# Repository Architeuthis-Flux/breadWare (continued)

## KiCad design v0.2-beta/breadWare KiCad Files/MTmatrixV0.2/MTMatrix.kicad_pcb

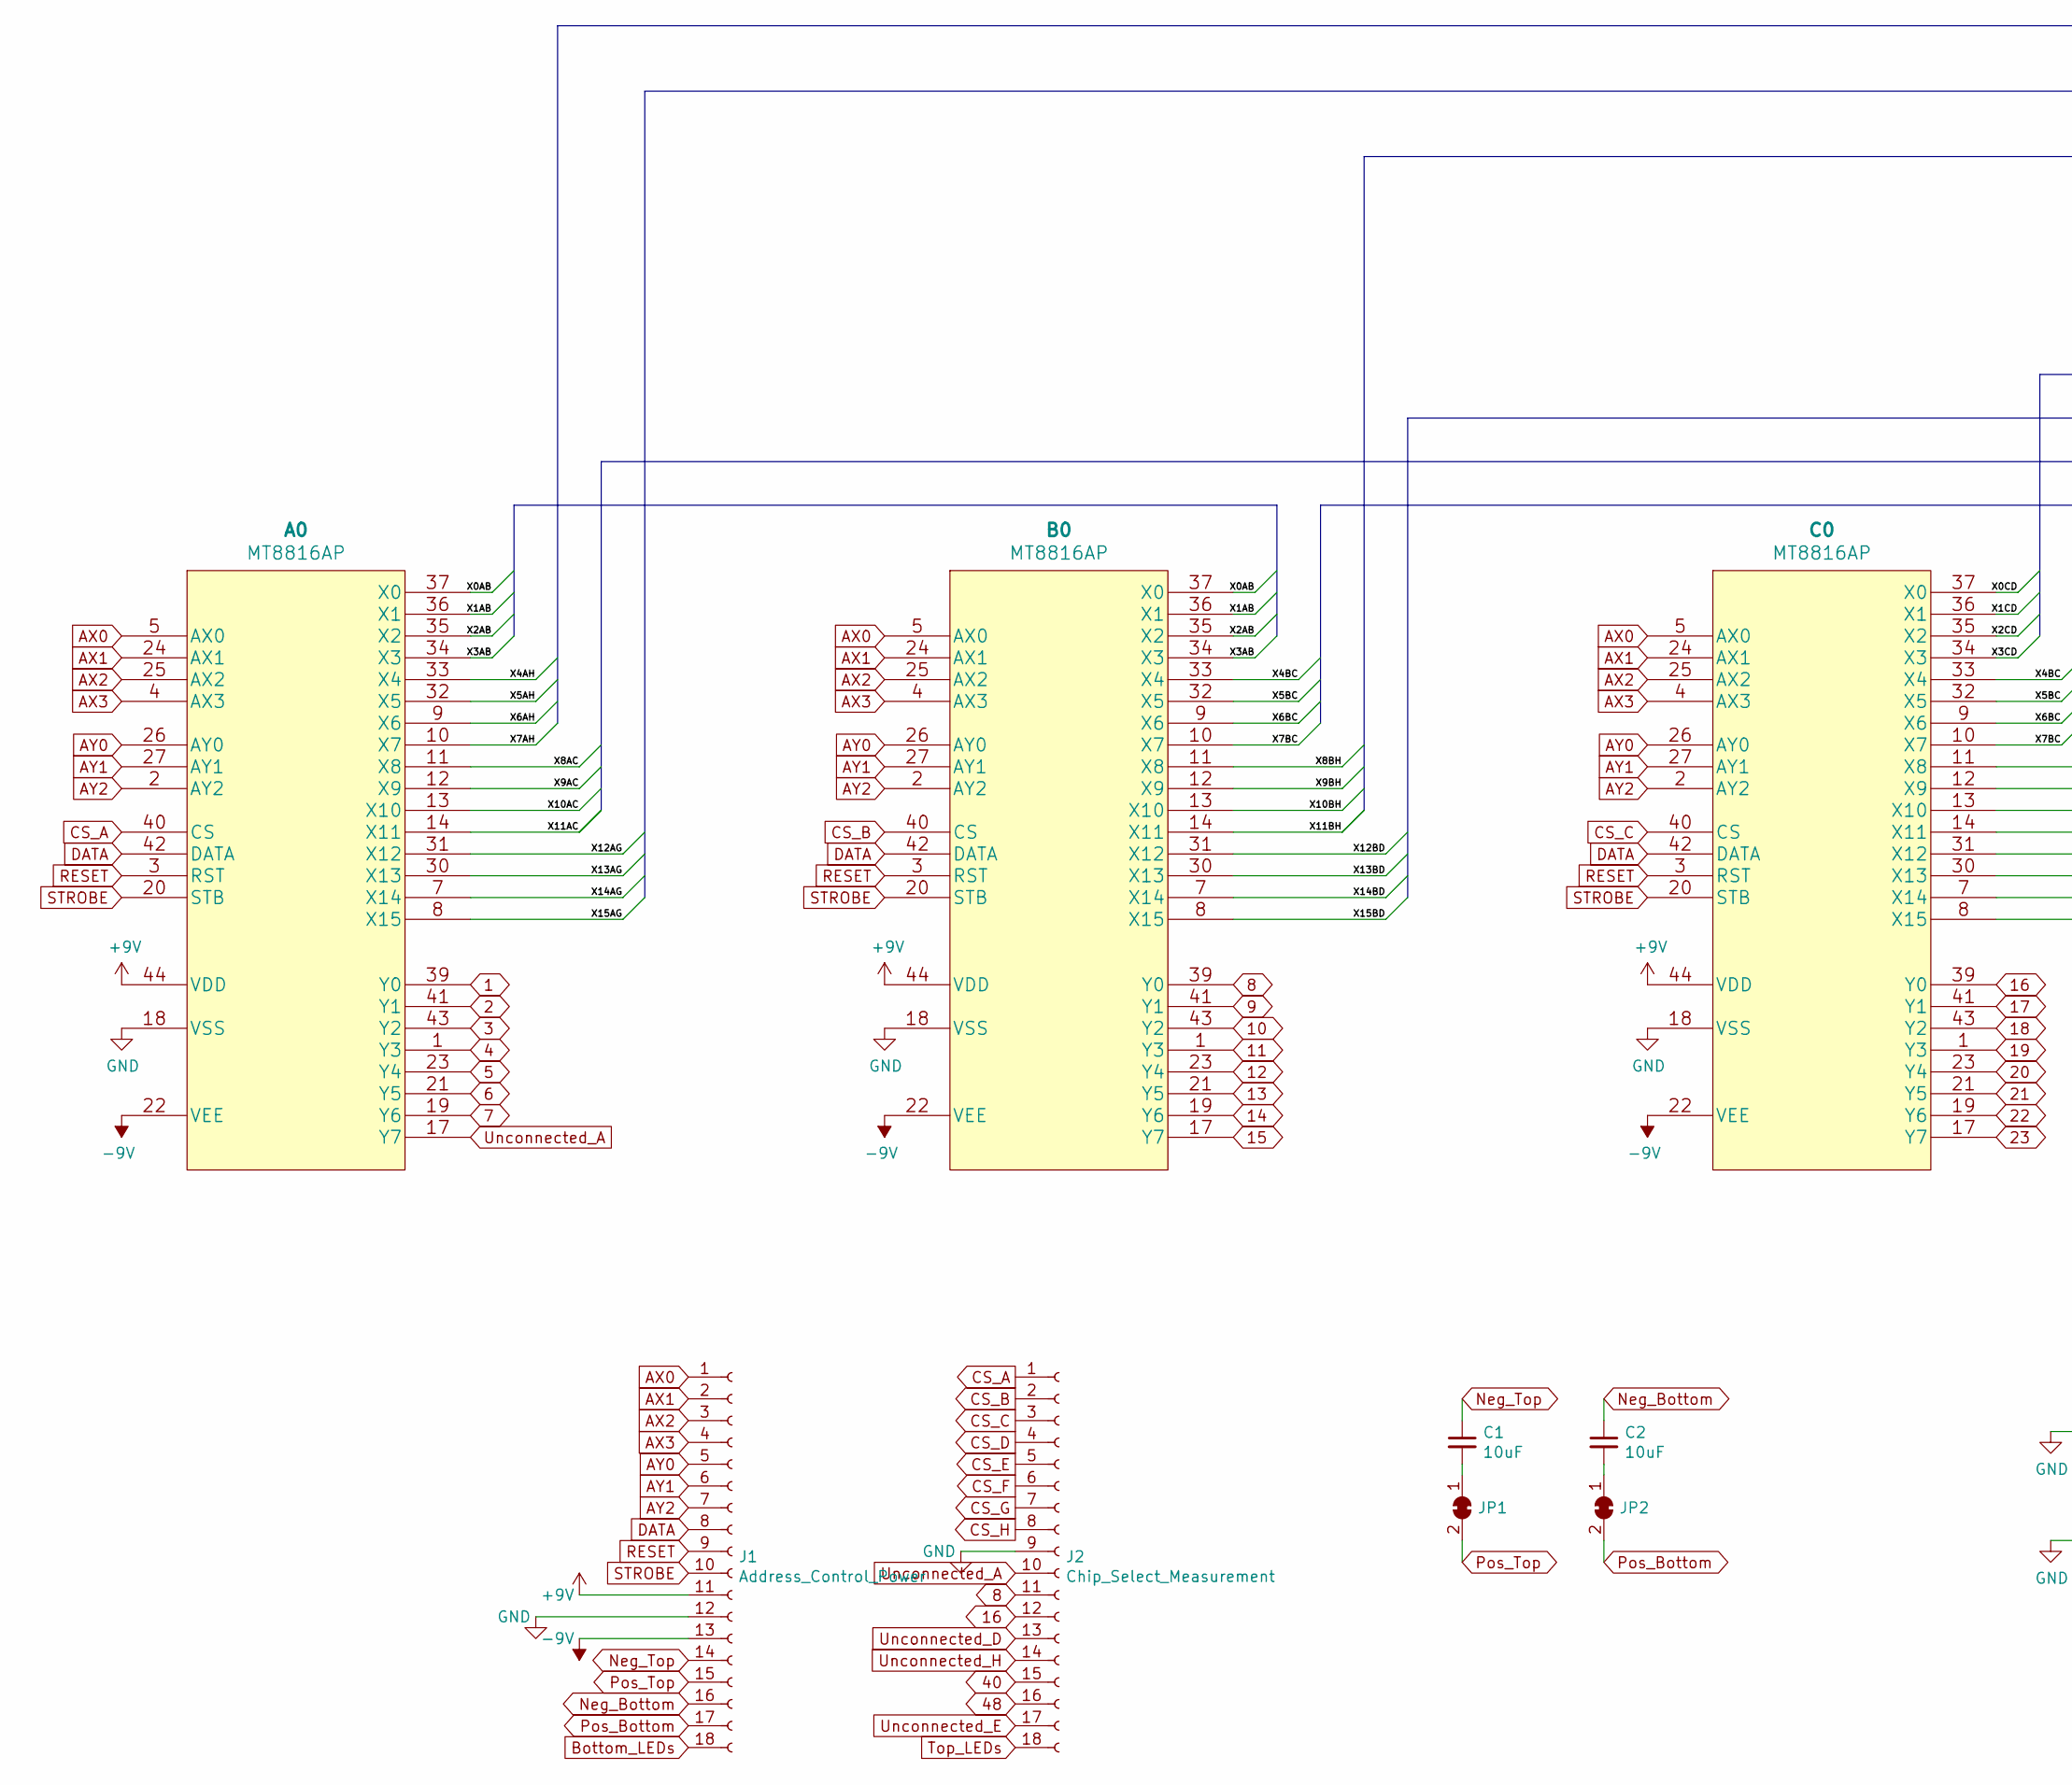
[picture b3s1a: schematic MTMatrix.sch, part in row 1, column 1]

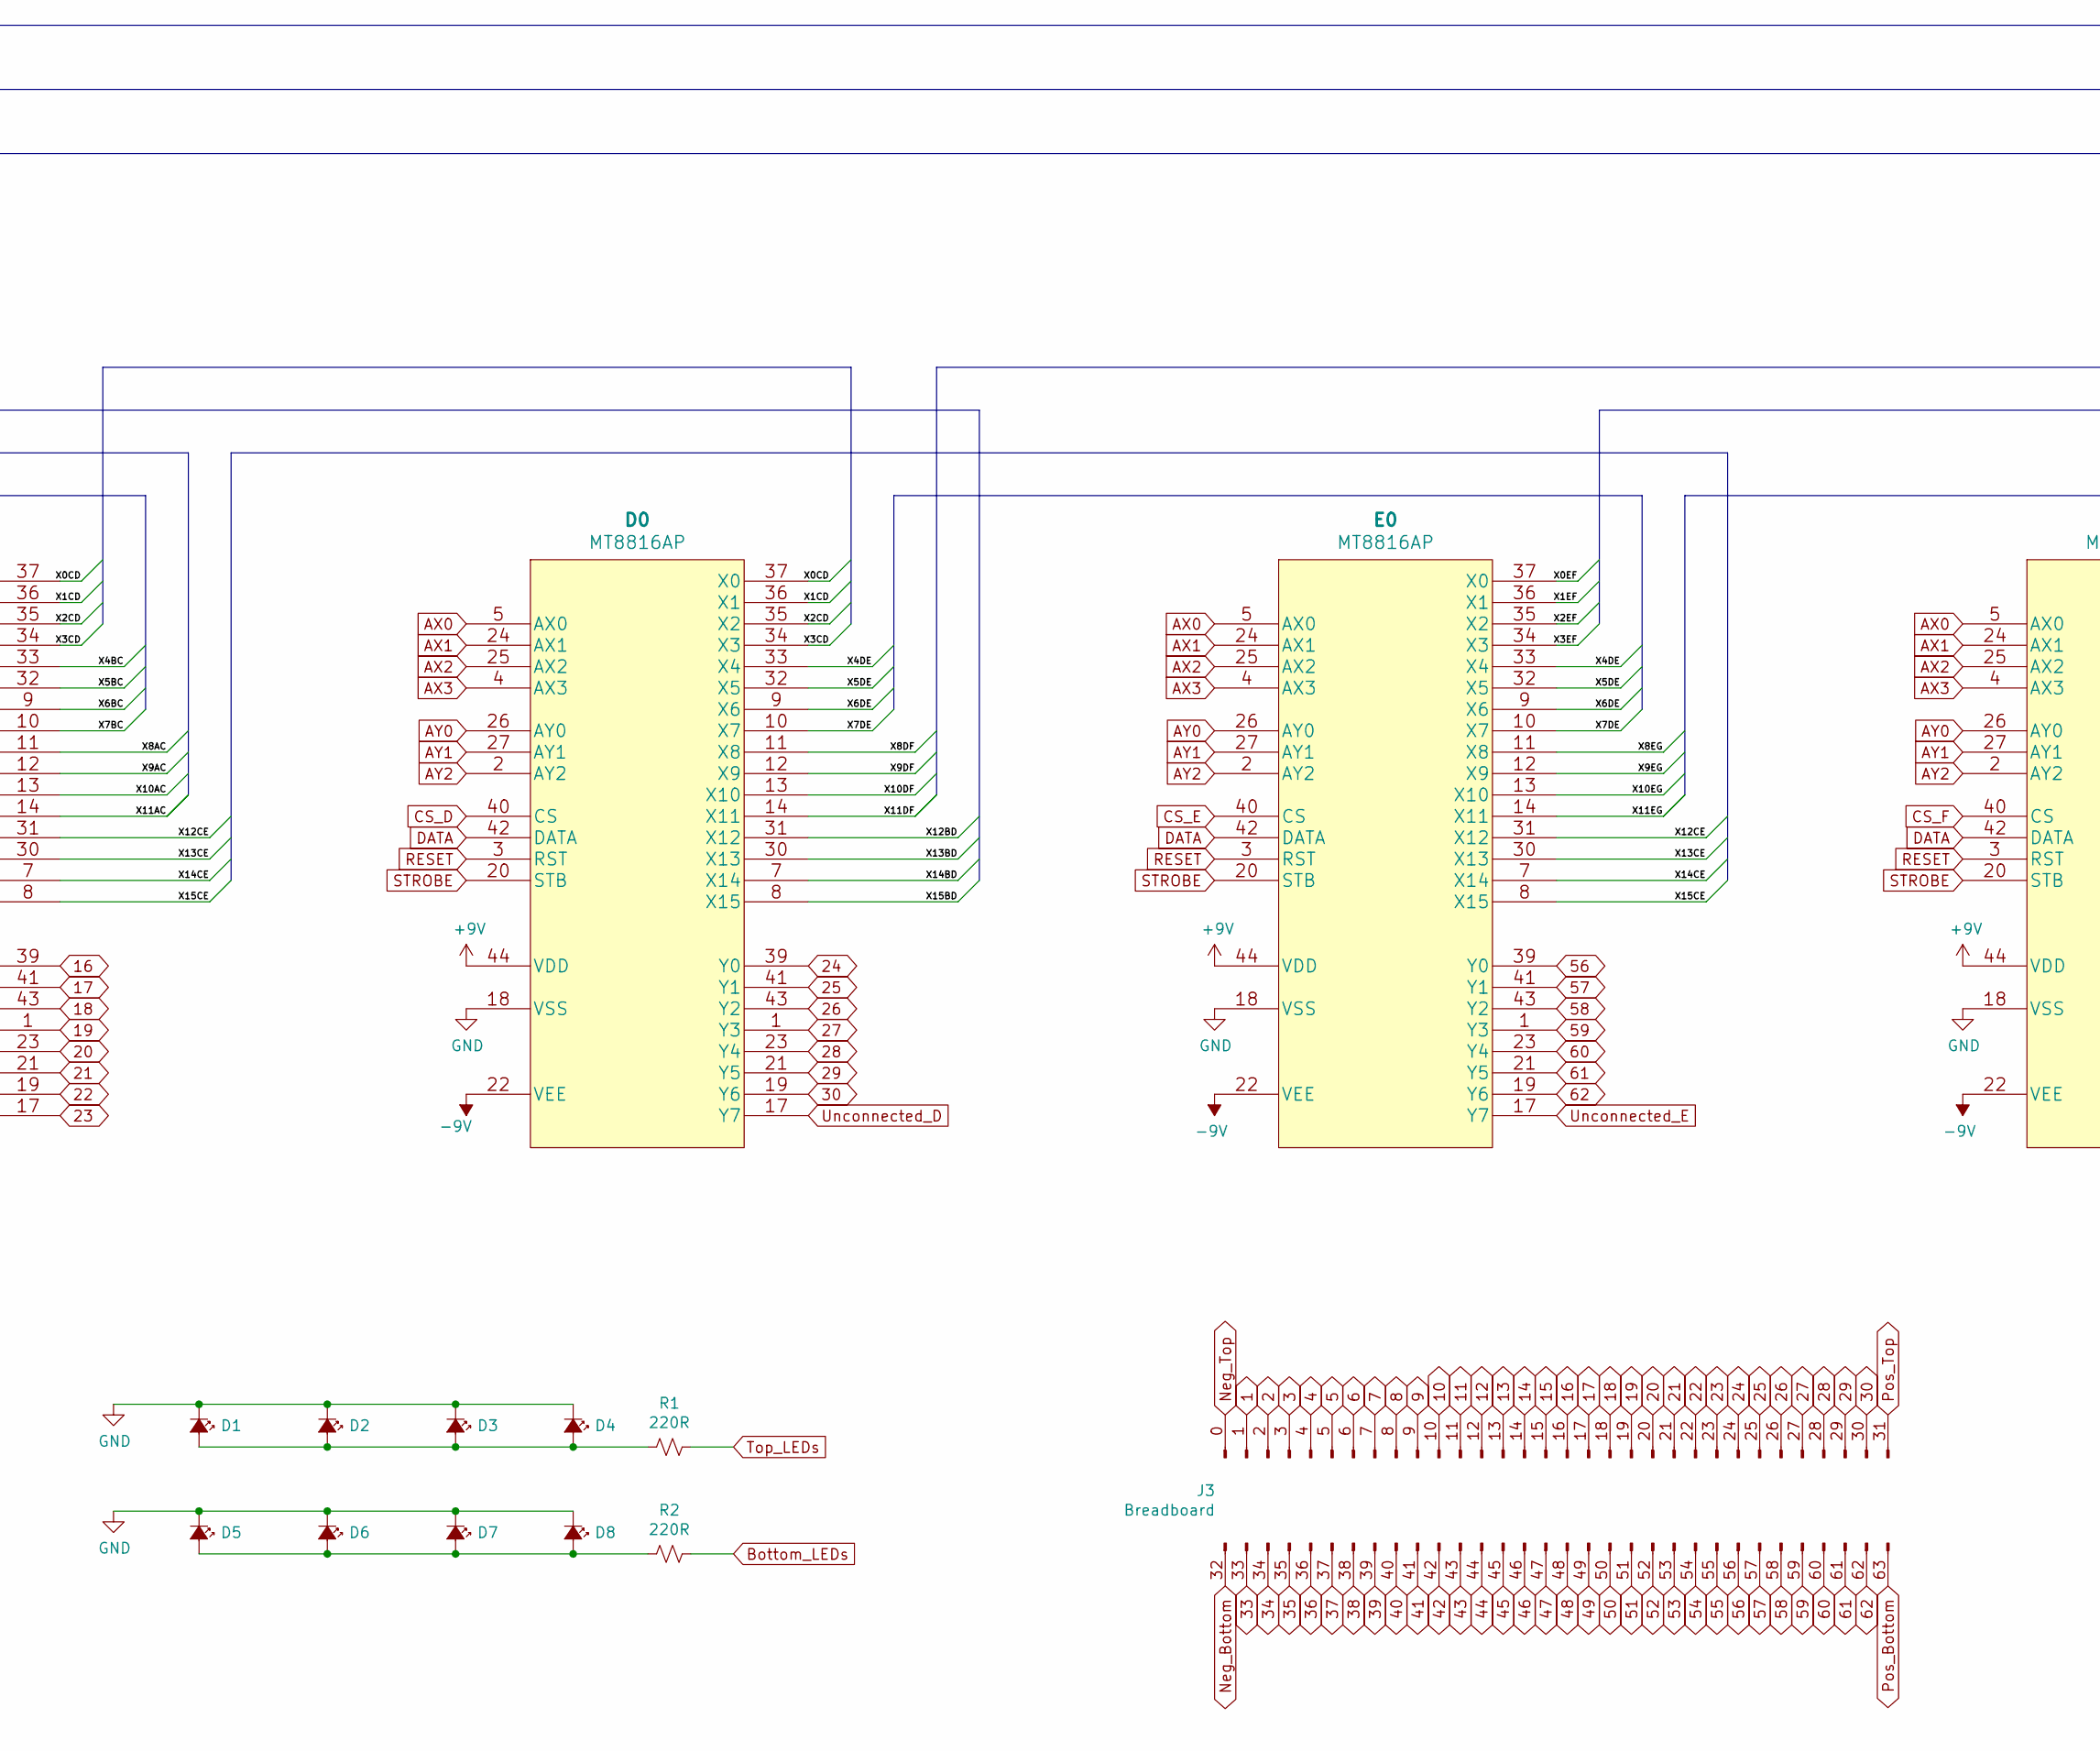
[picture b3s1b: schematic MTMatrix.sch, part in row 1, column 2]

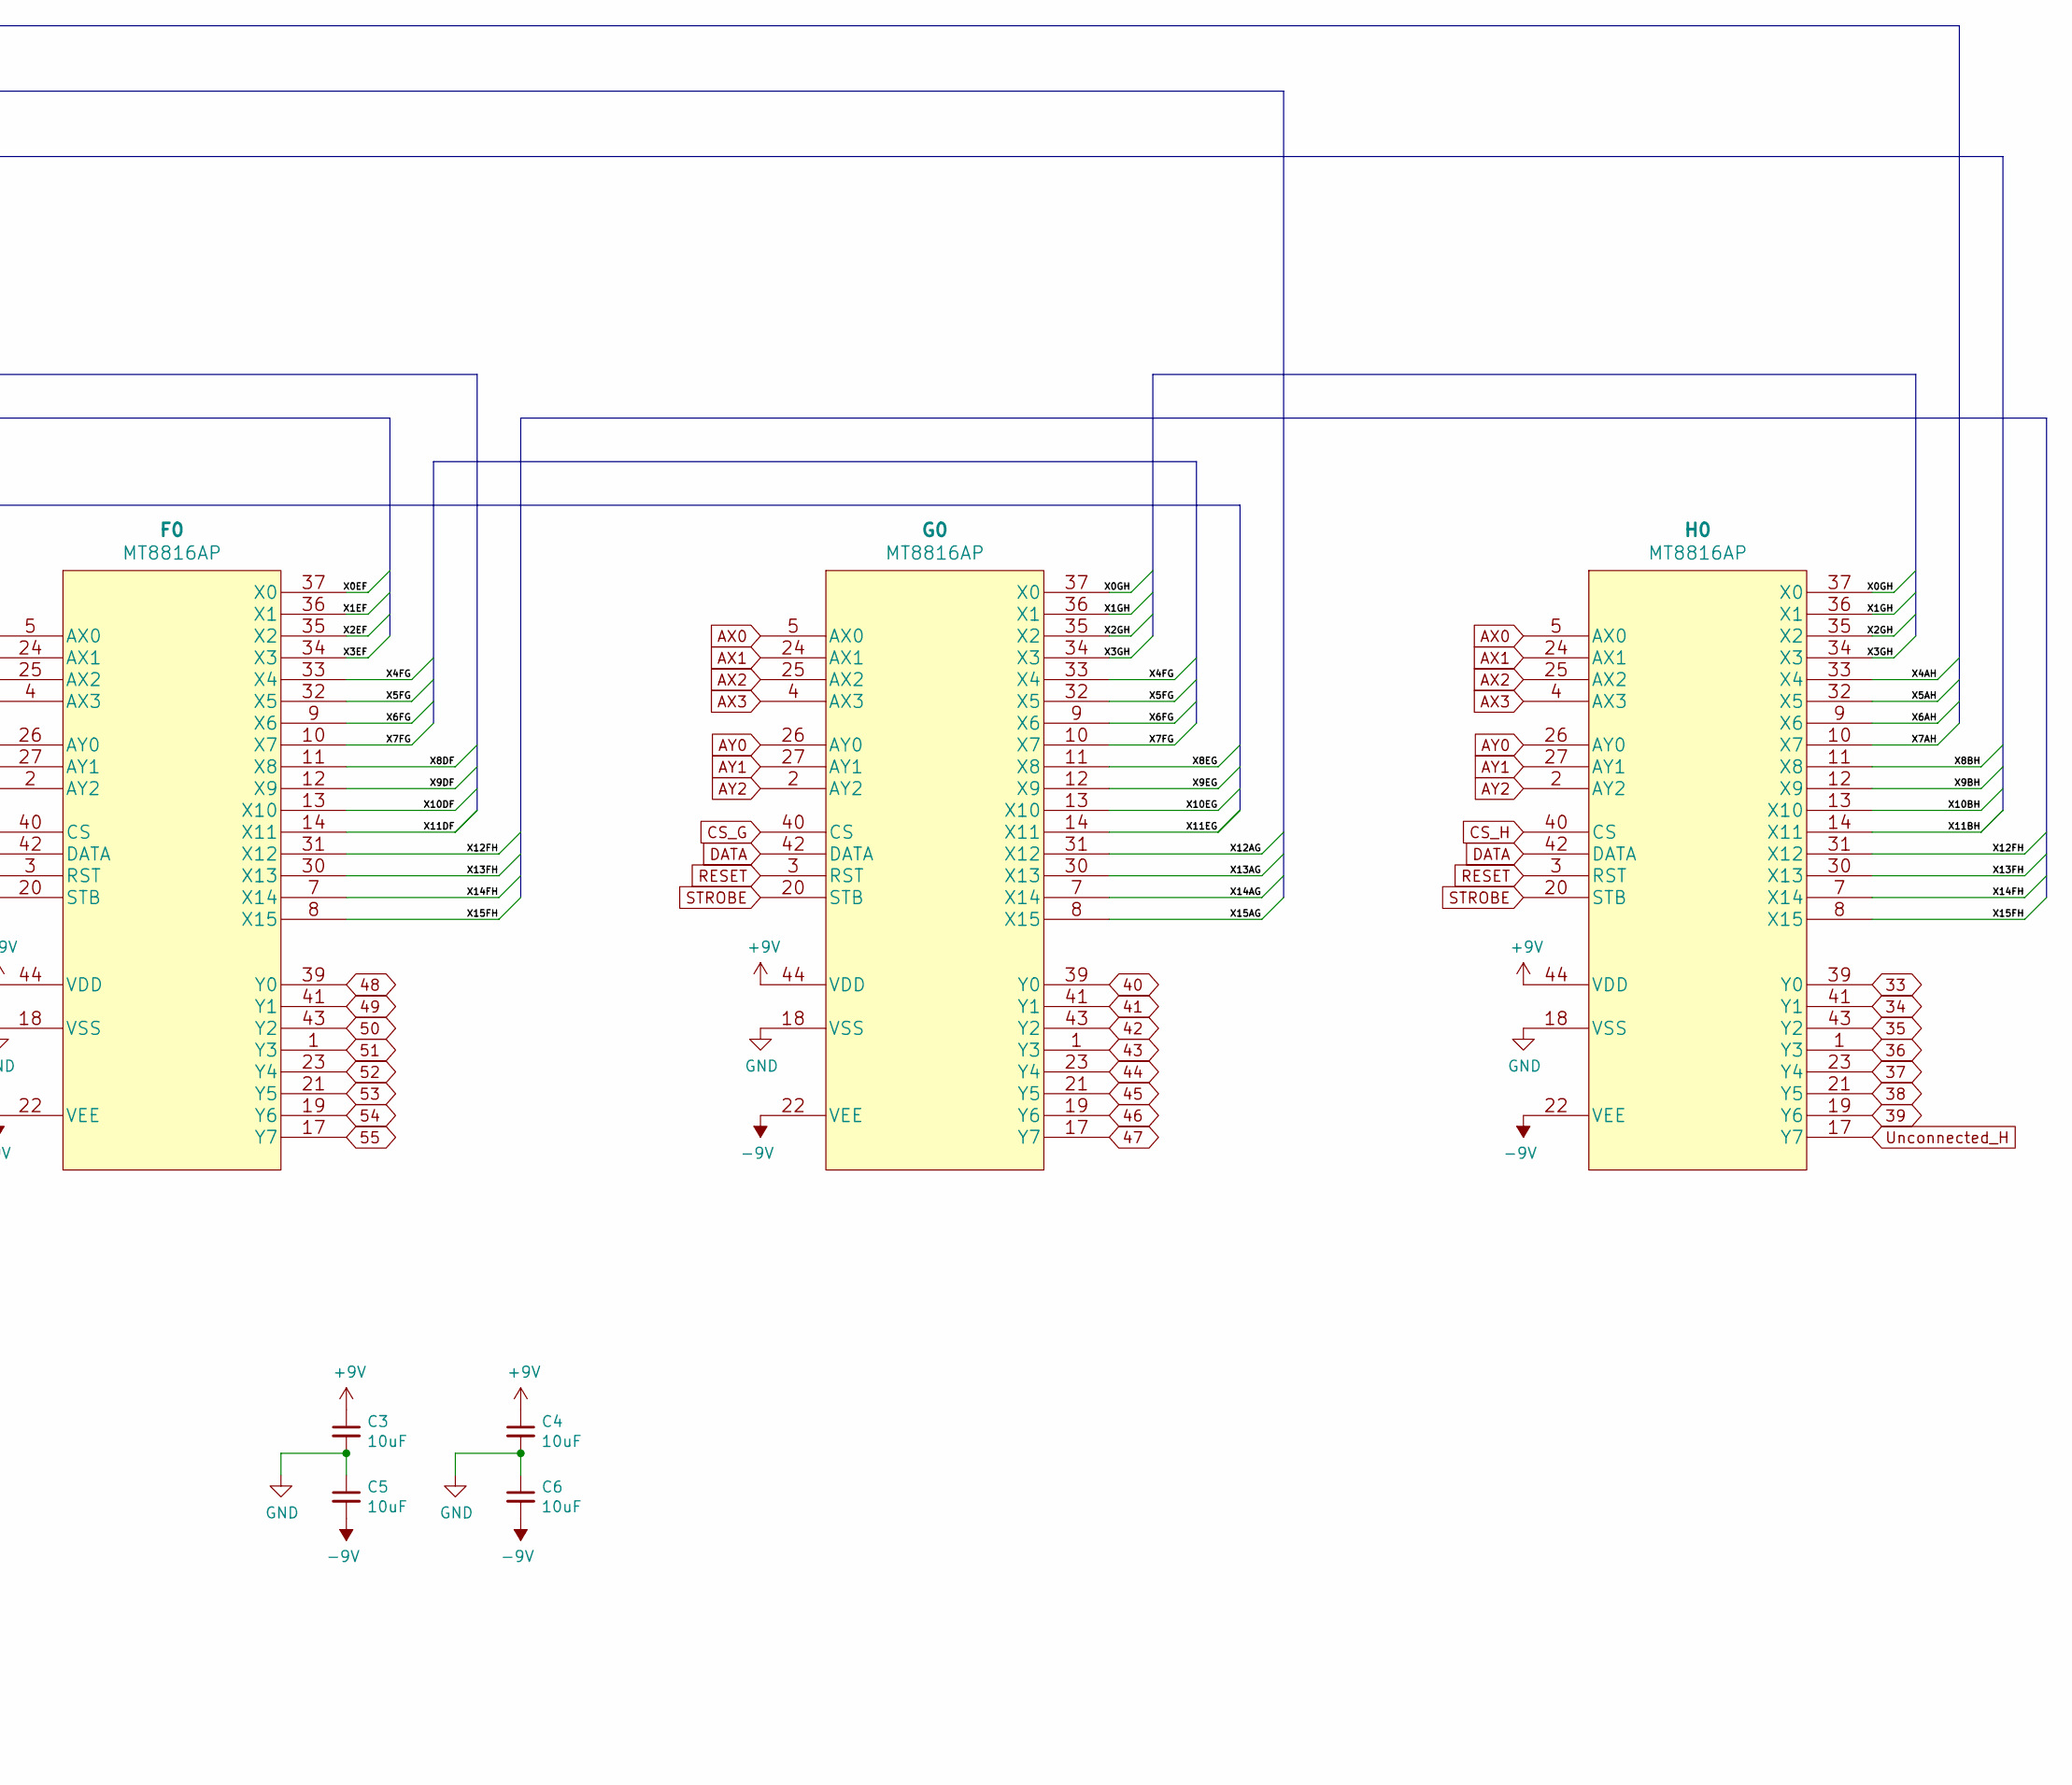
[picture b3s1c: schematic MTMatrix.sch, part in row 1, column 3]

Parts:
A0: MT8816AP; PLCC-44_16.6x16.6mm_P1.27mm
B0: MT8816AP; PLCC-44_16.6x16.6mm_P1.27mm
C0: MT8816AP; PLCC-44_16.6x16.6mm_P1.27mm
C1, C2, C3, C4, C5, C6: 10uF; C_0805_2012Metric_Pad1.15x1.40mm_HandSolder
D0: MT8816AP; PLCC-44_16.6x16.6mm_P1.27mm
D1, D2, D3, D4, D5, D6, D7, D8: LED_Small_ALT; LED_1206_3216Metric_ReverseMount_Hole1.8x2.4mm
E0: MT8816AP; PLCC-44_16.6x16.6mm_P1.27mm
F0: MT8816AP; PLCC-44_16.6x16.6mm_P1.27mm
G0: MT8816AP; PLCC-44_16.6x16.6mm_P1.27mm
H0: MT8816AP; PLCC-44_16.6x16.6mm_P1.27mm
J1: Address_Control_Power; PinHeader_1x18_P2.54mm_Vertical
J2: Chip_Select_Measurement; PinHeader_1x18_P2.54mm_Vertical
J3: Breadboard; Breadboard_Top
JP1, JP2: SolderJumper_2_Bridged; SolderJumper-2_P1.3mm_Bridged_RoundedPad1.0x1.5mm
R1, R2: 220R; R_0805_2012Metric_Pad1.15x1.40mm_HandSolder

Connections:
2: A0.41 (Y1), J3.2
3: A0.43 (Y2), J3.3
4: A0.1 (Y3), J3.4
5: A0.23 (Y4), J3.5
6: A0.21 (Y5), J3.6
7: A0.19 (Y6), J3.7
8: B0.39 (Y0), J2.11, J3.8
9: B0.41 (Y1), J3.9
10: B0.43 (Y2), J3.10
11: B0.1 (Y3), J3.11
12: B0.23 (Y4), J3.12
13: B0.21 (Y5), J3.13
14: B0.19 (Y6), J3.14
15: B0.17 (Y7), J3.15
16: C0.39 (Y0), J2.12, J3.16
17: C0.41 (Y1), J3.17
18: C0.43 (Y2), J3.18
19: C0.1 (Y3), J3.19
20: C0.23 (Y4), J3.20
21: C0.21 (Y5), J3.21
22: C0.19 (Y6), J3.22
23: C0.17 (Y7), J3.23
25: D0.41 (Y1), J3.25
26: D0.43 (Y2), J3.26
27: D0.1 (Y3), J3.27
28: D0.23 (Y4), J3.28
29: D0.21 (Y5), J3.29
30: D0.19 (Y6), J3.30
34: H0.41 (Y1), J3.34 (Pin_2)
35: H0.43 (Y2), J3.35 (Pin_3)
36: H0.1 (Y3), J3.36 (Pin_4)
37: H0.23 (Y4), J3.37 (Pin_5)
38: H0.21 (Y5), J3.38 (Pin_6)
39: H0.19 (Y6), J3.39 (Pin_7)
40: G0.39 (Y0), J2.15, J3.40 (Pin_8)
41: G0.41 (Y1), J3.41 (Pin_9)
42: G0.43 (Y2), J3.42 (Pin_10)
43: G0.1 (Y3), J3.43 (Pin_11)
44: G0.23 (Y4), J3.44 (Pin_12)
45: G0.21 (Y5), J3.45 (Pin_13)
46: G0.19 (Y6), J3.46 (Pin_14)
47: G0.17 (Y7), J3.47 (Pin_15)
48: F0.39 (Y0), J2.16, J3.48 (Pin_16)
49: F0.41 (Y1), J3.49 (Pin_17)
50: F0.43 (Y2), J3.50 (Pin_18)
51: F0.1 (Y3), J3.51 (Pin_19)
52: F0.23 (Y4), J3.52 (Pin_20)
53: F0.21 (Y5), J3.53 (Pin_21)
54: F0.19 (Y6), J3.54 (Pin_22)
55: F0.17 (Y7), J3.55 (Pin_23)
57: E0.41 (Y1), J3.57 (Pin_25)
58: E0.43 (Y2), J3.58 (Pin_26)
59: E0.1 (Y3), J3.59 (Pin_27)
60: E0.23 (Y4), J3.60 (Pin_28)
61: E0.21 (Y5), J3.61 (Pin_29)
62: E0.19 (Y6), J3.62 (Pin_30)
+9V: A0.44 (VDD), B0.44 (VDD), C0.44 (VDD), C3.1, C4.1, D0.44 (VDD), E0.44 (VDD), F0.44 (VDD), G0.44 (VDD), H0.44 (VDD), J1.11
-9V: A0.22 (VEE), B0.22 (VEE), C0.22 (VEE), C5.2, C6.2, D0.22 (VEE), E0.22 (VEE), F0.22 (VEE), G0.22 (VEE), H0.22 (VEE), J1.13
/X0AB: A0.37 (X0), B0.37 (X0)
/X0CD: C0.37 (X0), D0.37 (X0)
/X0EF: E0.37 (X0), F0.37 (X0)
/X0GH: G0.37 (X0), H0.37 (X0)
/X1AB: A0.36 (X1), B0.36 (X1)
/X1CD: C0.36 (X1), D0.36 (X1)
/X1EF: E0.36 (X1), F0.36 (X1)
/X1GH: G0.36 (X1), H0.36 (X1)
/X2AB: A0.35 (X2), B0.35 (X2)
/X2CD: C0.35 (X2), D0.35 (X2)
/X2EF: E0.35 (X2), F0.35 (X2)
/X2GH: G0.35 (X2), H0.35 (X2)
/X3AB: A0.34 (X3), B0.34 (X3)
/X3CD: C0.34 (X3), D0.34 (X3)
/X3EF: E0.34 (X3), F0.34 (X3)
/X3GH: G0.34 (X3), H0.34 (X3)
/X4AH: A0.33 (X4), H0.33 (X4)
/X4BC: B0.33 (X4), C0.33 (X4)
/X4DE: D0.33 (X4), E0.33 (X4)
/X4FG: F0.33 (X4), G0.33 (X4)
/X5AH: A0.32 (X5), H0.32 (X5)
/X5BC: B0.32 (X5), C0.32 (X5)
/X5DE: D0.32 (X5), E0.32 (X5)
/X5FG: F0.32 (X5), G0.32 (X5)
/X6AH: A0.9 (X6), H0.9 (X6)
/X6BC: B0.9 (X6), C0.9 (X6)
/X6DE: D0.9 (X6), E0.9 (X6)
/X6FG: F0.9 (X6), G0.9 (X6)
/X7AH: A0.10 (X7), H0.10 (X7)
/X7BC: B0.10 (X7), C0.10 (X7)
/X7DE: D0.10 (X7), E0.10 (X7)
/X7FG: F0.10 (X7), G0.10 (X7)
/X8AC: A0.11 (X8), C0.11 (X8)
/X8BH: B0.11 (X8), H0.11 (X8)
/X8DF: D0.11 (X8), F0.11 (X8)
/X8EG: E0.11 (X8), G0.11 (X8)
/X9AC: A0.12 (X9), C0.12 (X9)
/X9BH: B0.12 (X9), H0.12 (X9)
/X9DF: D0.12 (X9), F0.12 (X9)
/X9EG: E0.12 (X9), G0.12 (X9)
/X10AC: A0.13 (X10), C0.13 (X10)
/X10BH: B0.13 (X10), H0.13 (X10)
/X10DF: D0.13 (X10), F0.13 (X10)
/X10EG: E0.13 (X10), G0.13 (X10)
/X11AC: A0.14 (X11), C0.14 (X11)
/X11BH: B0.14 (X11), H0.14 (X11)
/X11DF: D0.14 (X11), F0.14 (X11)
/X11EG: E0.14 (X11), G0.14 (X11)
/X12AG: A0.31 (X12), G0.31 (X12)
/X12BD: B0.31 (X12), D0.31 (X12)
/X12CE: C0.31 (X12), E0.31 (X12)
/X12FH: F0.31 (X12), H0.31 (X12)
/X13AG: A0.30 (X13), G0.30 (X13)
/X13BD: B0.30 (X13), D0.30 (X13)
/X13CE: C0.30 (X13), E0.30 (X13)
/X13FH: F0.30 (X13), H0.30 (X13)
/X14AG: A0.7 (X14), G0.7 (X14)
/X14BD: B0.7 (X14), D0.7 (X14)
/X14CE: C0.7 (X14), E0.7 (X14)
/X14FH: F0.7 (X14), H0.7 (X14)
/X15AG: A0.8 (X15), G0.8 (X15)
/X15BD: B0.8 (X15), D0.8 (X15)
/X15CE: C0.8 (X15), E0.8 (X15)
/X15FH: F0.8 (X15), H0.8 (X15)
AX0: A0.5 (AX0), B0.5 (AX0), C0.5 (AX0), D0.5 (AX0), E0.5 (AX0), F0.5 (AX0), G0.5 (AX0), H0.5 (AX0), J1.1
AX1: A0.24 (AX1), B0.24 (AX1), C0.24 (AX1), D0.24 (AX1), E0.24 (AX1), F0.24 (AX1), G0.24 (AX1), H0.24 (AX1), J1.2
AX2: A0.25 (AX2), B0.25 (AX2), C0.25 (AX2), D0.25 (AX2), E0.25 (AX2), F0.25 (AX2), G0.25 (AX2), H0.25 (AX2), J1.3
AX3: A0.4 (AX3), B0.4 (AX3), C0.4 (AX3), D0.4 (AX3), E0.4 (AX3), F0.4 (AX3), G0.4 (AX3), H0.4 (AX3), J1.4
AY0: A0.26 (AY0), B0.26 (AY0), C0.26 (AY0), D0.26 (AY0), E0.26 (AY0), F0.26 (AY0), G0.26 (AY0), H0.26 (AY0), J1.5
AY1: A0.27 (AY1), B0.27 (AY1), C0.27 (AY1), D0.27 (AY1), E0.27 (AY1), F0.27 (AY1), G0.27 (AY1), H0.27 (AY1), J1.6
AY2: A0.2 (AY2), B0.2 (AY2), C0.2 (AY2), D0.2 (AY2), E0.2 (AY2), F0.2 (AY2), G0.2 (AY2), H0.2 (AY2), J1.7
Bottom_LEDs: J1.18, R2.1
CS_A: A0.40 (CS), J2.1
CS_B: B0.40 (CS), J2.2
CS_C: C0.40 (CS), J2.3
CS_D: D0.40 (CS), J2.4
CS_E: E0.40 (CS), J2.5
CS_F: F0.40 (CS), J2.6
CS_G: G0.40 (CS), J2.7
CS_H: H0.40 (CS), J2.8
DATA: A0.42 (DATA), B0.42 (DATA), C0.42 (DATA), D0.42 (DATA), E0.42 (DATA), F0.42 (DATA), G0.42 (DATA), H0.42 (DATA), J1.8
GND: A0.18 (VSS), B0.18 (VSS), C0.18 (VSS), C3.2, C4.2, C5.1, C6.1, D0.18 (VSS), D1.1 (K), D2.1 (K), D3.1 (K), D4.1 (K), D5.1 (K), D6.1 (K), D7.1 (K), D8.1 (K), E0.18 (VSS), F0.18 (VSS), G0.18 (VSS), H0.18 (VSS), J1.12, J2.9
Neg_Bottom: C2.1, J1.16, J3.32 (Pin_0)
Neg_Top: C1.1, J1.14, J3.0
unnamed: C1.2, JP1.1 (A)
unnamed: C2.2, JP2.1 (A)
unnamed: D1.2 (A), D2.2 (A), D3.2 (A), D4.2 (A), R1.2
unnamed: D5.2 (A), D6.2 (A), D7.2 (A), D8.2 (A), R2.2
Pos_Bottom: J1.17, J3.63 (Pin_31), JP2.2 (B)
Pos_Top: J1.15, J3.31, JP1.2 (B)
RESET: A0.3 (RST), B0.3 (RST), C0.3 (RST), D0.3 (RST), E0.3 (RST), F0.3 (RST), G0.3 (RST), H0.3 (RST), J1.9
STROBE: A0.20 (STB), B0.20 (STB), C0.20 (STB), D0.20 (STB), E0.20 (STB), F0.20 (STB), G0.20 (STB), H0.20 (STB), J1.10
Top_LEDs: J2.18, R1.1

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
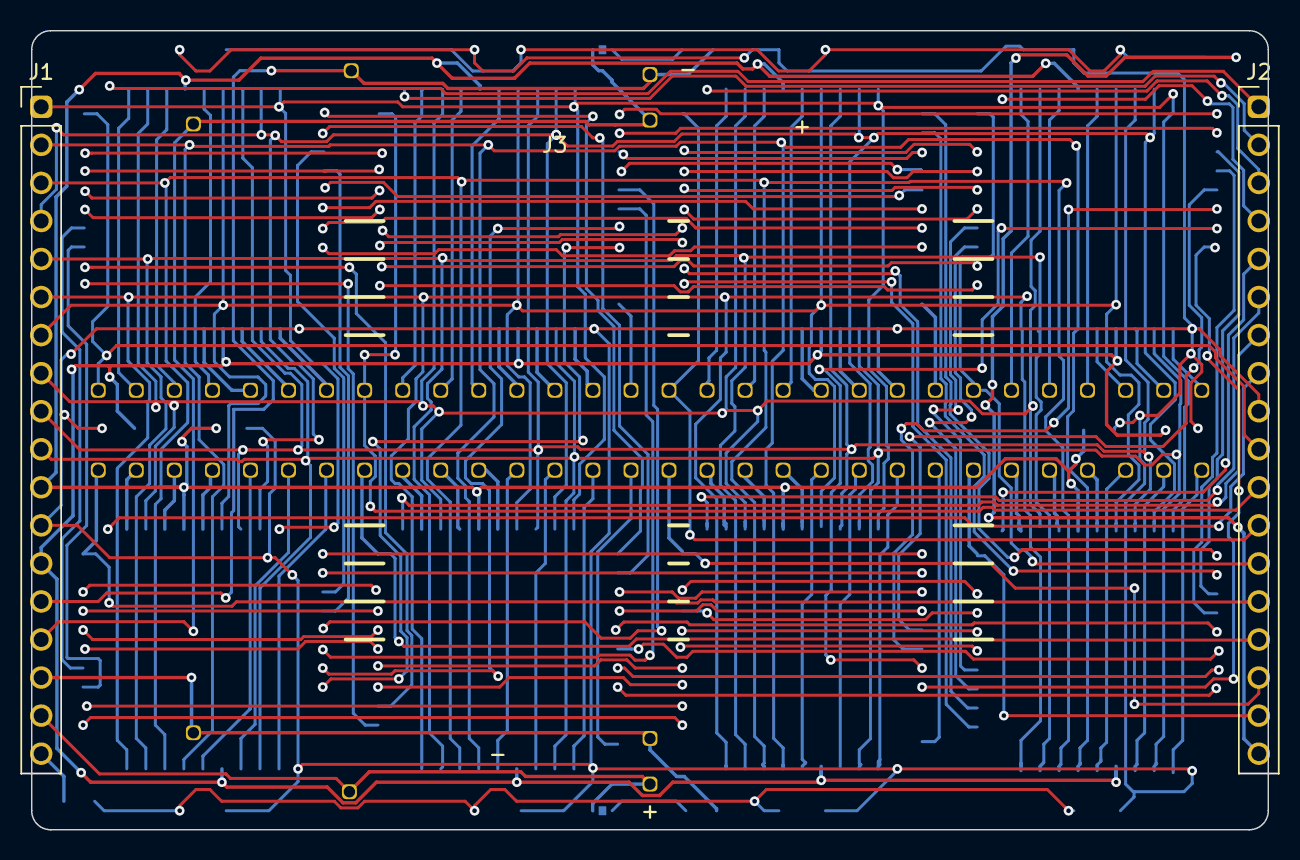
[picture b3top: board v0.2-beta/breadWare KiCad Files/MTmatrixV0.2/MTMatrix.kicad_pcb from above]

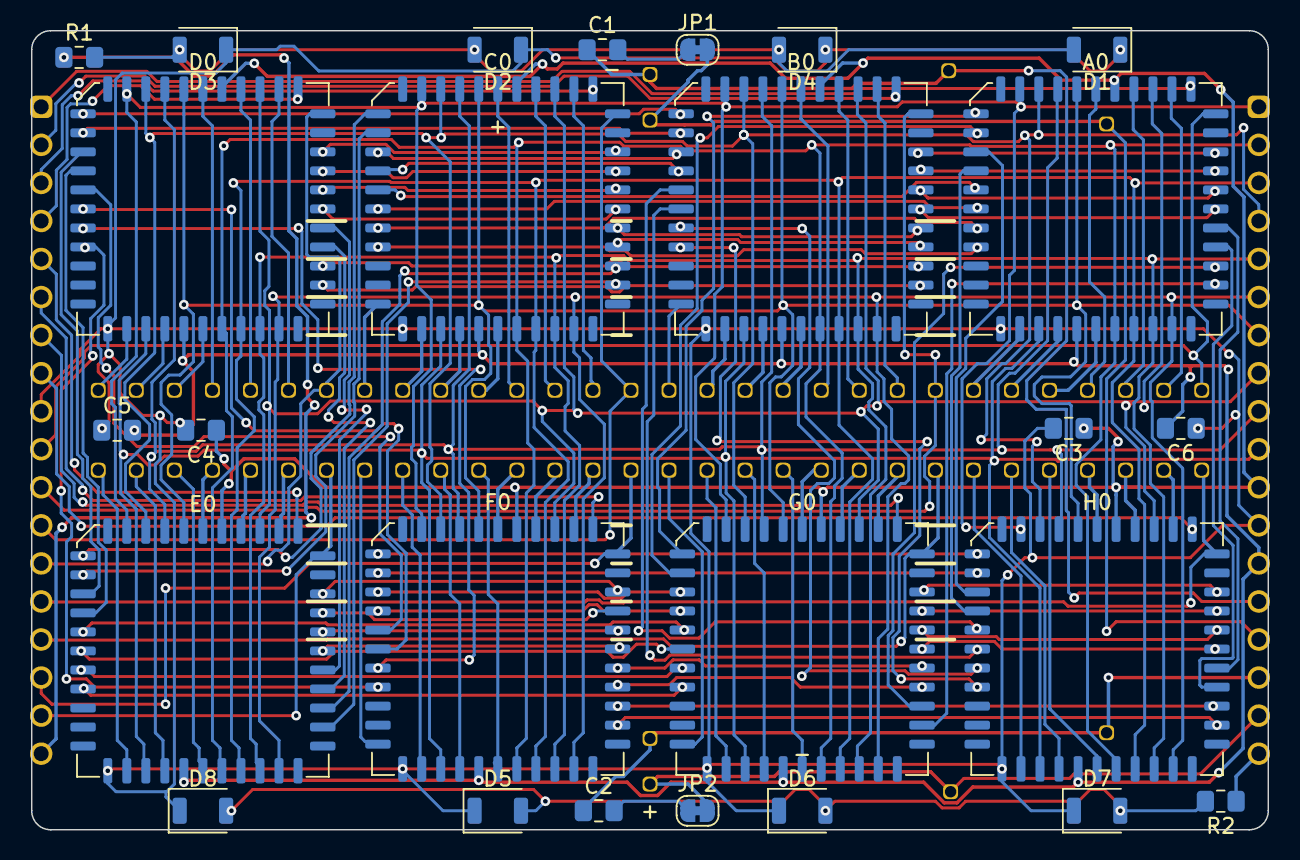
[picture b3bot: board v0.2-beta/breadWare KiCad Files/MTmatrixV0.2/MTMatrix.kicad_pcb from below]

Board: 2 copper layers, 82.5 x 53.3 mm, 29 parts (26 on the bottom side), 155 nets.
